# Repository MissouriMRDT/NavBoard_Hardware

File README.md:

# MRDT NavBoard Hardware

## Purpose
The Navigation (Nav) Board is responsible for containing, supplying, and interfacing the equipment required to determine the rover's position and orientation. This board does this by utilizing 2 inertial measurement units (IMUs) and a connection to an external GPS receiver. This data is processed and sent to the rest of the rover via an ethernet connection.
## Design

This revision of the board is a new design, based on the components and connections from the 2022/2023 Rev 2 designs. The goal of this design was to make the board as small as possible, and to mount onto a Teensy 4.1 instead of a raspberry pi.

This design utilizes a 4-layer PCB with holes for M3 mounting screws on 15mm standoffs. The Teensy is soldered onto one side of the board, and all of the smd components are mounted on the other side.

This design also includes an ethernet RJ45 jack for allowing ethernet connectivity to the Teensy.

## Required External Connections
 - +12V
 - GPS (I2C and UART)
 - Teensy 4.1
 - Ethernet

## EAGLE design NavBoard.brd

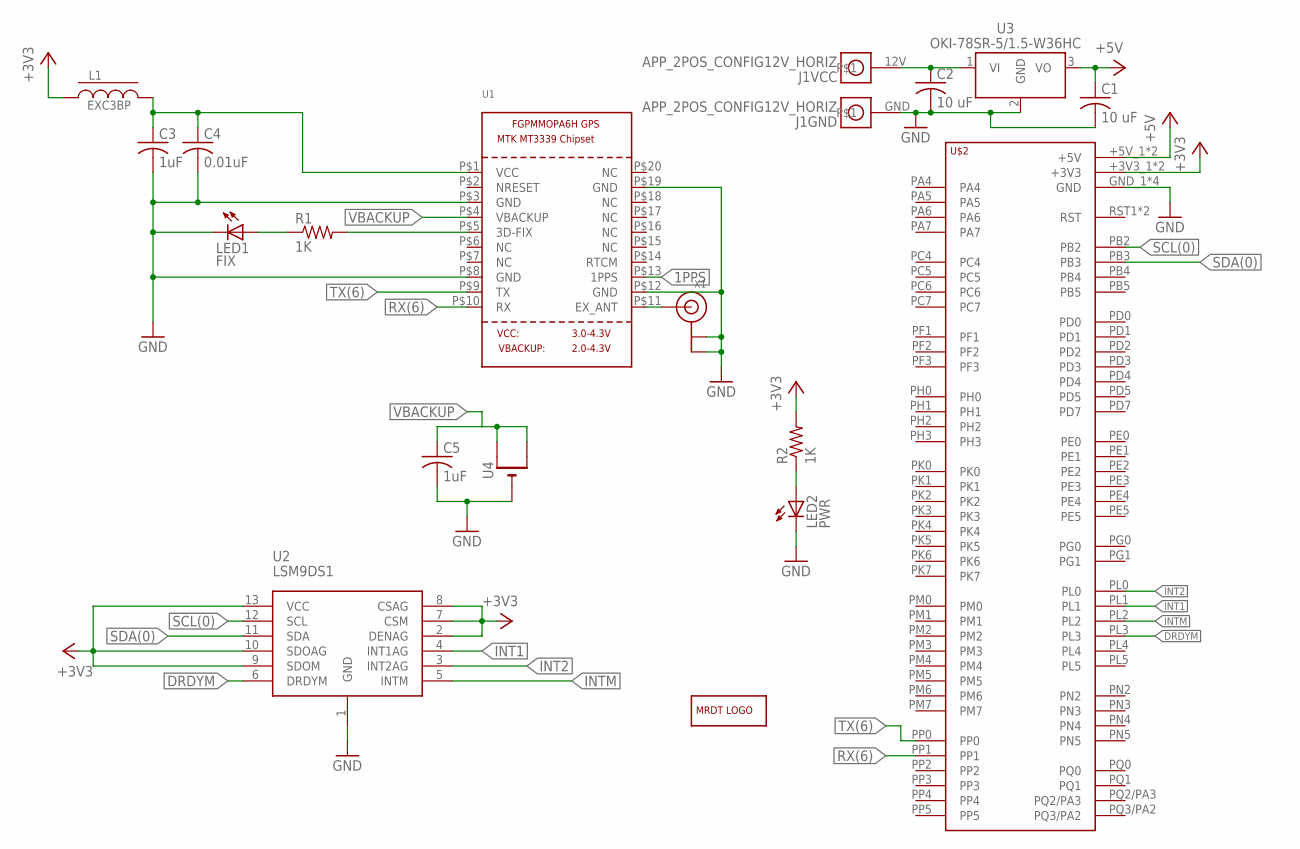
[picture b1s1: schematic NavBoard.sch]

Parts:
C1, C2: 10 uF; C1206
C3, C5: 1uF; C0805
C4: 0.01uF; C0805
J1: APP_2POS_CONFIG12V_HORIZ; APP45_12V_HORIZ_CONFIG
L1: EXC3BP; L0603
LED1: FIX; CHIPLED_0805
LED2: PWR; CHIPLED_0805
LOGO1: MRDT_LOGO
R1, R2: 1K; M0805
U1: GPS_FGPMMOPA6H; FGPMMOPA6H
U2: LSM9DS1; LSM9DS1_BREAKOUT
U3: OKI-78SR-5/1.5-W36HC; OKI-78SR_HORIZ
U4: CR1220SMT; CR1220-SMD
U$2: TIVA-1294; TIVA-C-CONNECTED
X1: ANTENNA_U.FL; U.FL

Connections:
1PPS: U1.P$13 (1PPS)
+3V3: L1.1, R2.2, U2.2 (DENAG), U2.7 (CSM), U2.8 (CSAG), U2.9 (SDOM), U2.10 (SDOAG), U2.13 (VCC), U$2.+3V3_1 (+3V3), U$2.+3V3_2 (+3V3)
+5V: C1.1, U3.3 (VO), U$2.+5V_1 (+5V), U$2.+5V_2 (+5V)
DRDYM: U2.6 (DRDYM), U$2.PL3
GND: C1.2, C2.2, C3.2, C4.2, C5.2, J1.GND, LED1.C, LED2.C, U1.P$3 (GND), U1.P$8 (GND), U1.P$12 (GND), U1.P$19 (GND), U2.1 (GND), U3.2 (GND), U4.-, U$2.GND_1 (GND), U$2.GND_2 (GND), U$2.GND_3 (GND), U$2.GND_4 (GND), X1.1 (GND), X1.2 (GND)
INT1: U2.4 (INT1AG), U$2.PL1
INT2: U2.3 (INT2AG), U$2.PL0
INTM: U2.5 (INTM), U$2.PL2
unnamed: C2.1, J1.12V, U3.1 (VI)
unnamed: LED1.A, R1.1
unnamed: R1.2, U1.P$5 (3D-FIX)
unnamed: LED2.A, R2.1
unnamed: U1.P$11 (EX_ANT), X1.3 (SIGNAL)
unnamed: C3.1, C4.1, L1.2, U1.P$1 (VCC)
RX(6): U1.P$10 (RX), U$2.PP1
SCL(0): U2.12 (SCL), U$2.PB2
SDA(0): U2.11 (SDA), U$2.PB3
TX(6): U1.P$9 (TX), U$2.PP0
VBACKUP: C5.1, U1.P$4 (VBACKUP), U4.+$1 (+), U4.+$2 (+1)

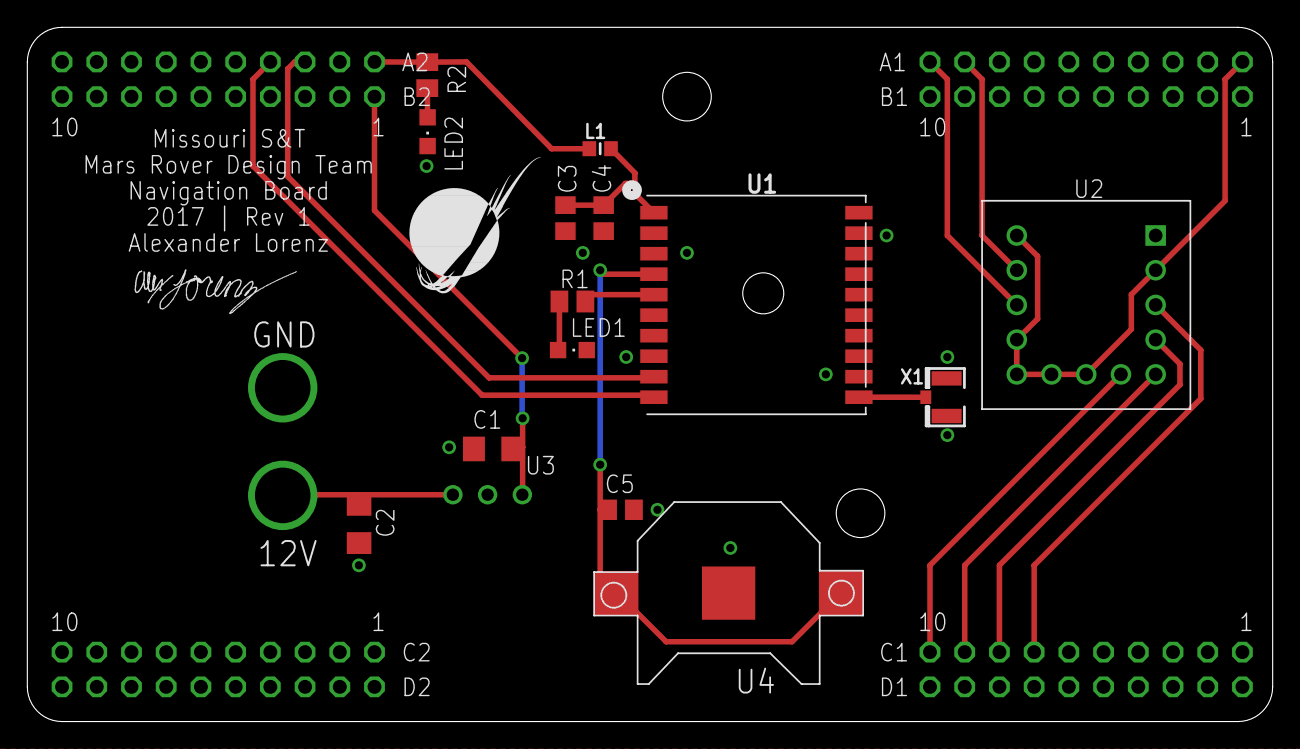
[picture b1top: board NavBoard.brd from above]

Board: 2 copper layers, 91.1 x 50.8 mm, 21 parts (0 on the bottom side), 18 nets.

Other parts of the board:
U$1: SIG
U$3, U$4: #6_SCREW

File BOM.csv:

Part,Value,Device,Package,Description,COLOR1,COLOR2,VOUT
C1,10 uF,C-USC1206,C1206,"CAPACITOR, American symbol",,,
C2,10 uF,C-USC1206,C1206,"CAPACITOR, American symbol",,,
C3,1uF,C-USC0805,C0805,"CAPACITOR, American symbol",,,
C4,0.01uF,C-USC0805,C0805,"CAPACITOR, American symbol",,,
C5,1uF,C-USC0805,C0805,"CAPACITOR, American symbol",,,
J1,APP_2POS_CONFIG12V_HORIZ,APP_2POS_CONFIG12V_HORIZ,APP45_12V_HORIZ_CONFIG,,YELLOW,BLACK,
L1,EXC3BP,EXC3BP,L0603,"gPS Module - MTK MT3339 Chipset, -165dBm sensitivity, 22 channels, 10Hz, auto-select external antenna options",,,
LED1,FIX,LEDCHIPLED_0805,CHIPLED_0805,LED,,,
LED2,PWR,LEDCHIPLED_0805,CHIPLED_0805,LED,,,
LOGO1,MRDT_LOGO,MRDT_LOGO,MRDT_LOGO,,,,
R1,1K,R-US_M0805,M0805,"RESISTOR, American symbol",,,
R2,1K,R-US_M0805,M0805,"RESISTOR, American symbol",,,
U$2,TIVA-1294,TIVA-1294,TIVA-C-CONNECTED,TIVA C CONNECTED LAUNCHPAD,,,
U1,,GPS_FGPMMOPA6H,FGPMMOPA6H,"GPS Module - MTK MT3339 Chipset, -165dBm sensitivity, 22 channels, 10Hz, auto-select external antenna options",,,
U2,LSM9DS1,LSM9DS1,LSM9DS1_BREAKOUT,,,,
U3,OKI-78SR-5/1.5-W36HC,OKI-78SR-5/1.5-W36HC,OKI-78SR_HORIZ,4.95W DC/DC Converter,,,+5v
U4,,CR1220SMT,CR1220-SMD,CR1216/CR1220/CR1225 12mm 3V lithium coin cell,,,
X1,,ANTENNA_U.FL,U.FL,U.FL Antenna Connector,,,

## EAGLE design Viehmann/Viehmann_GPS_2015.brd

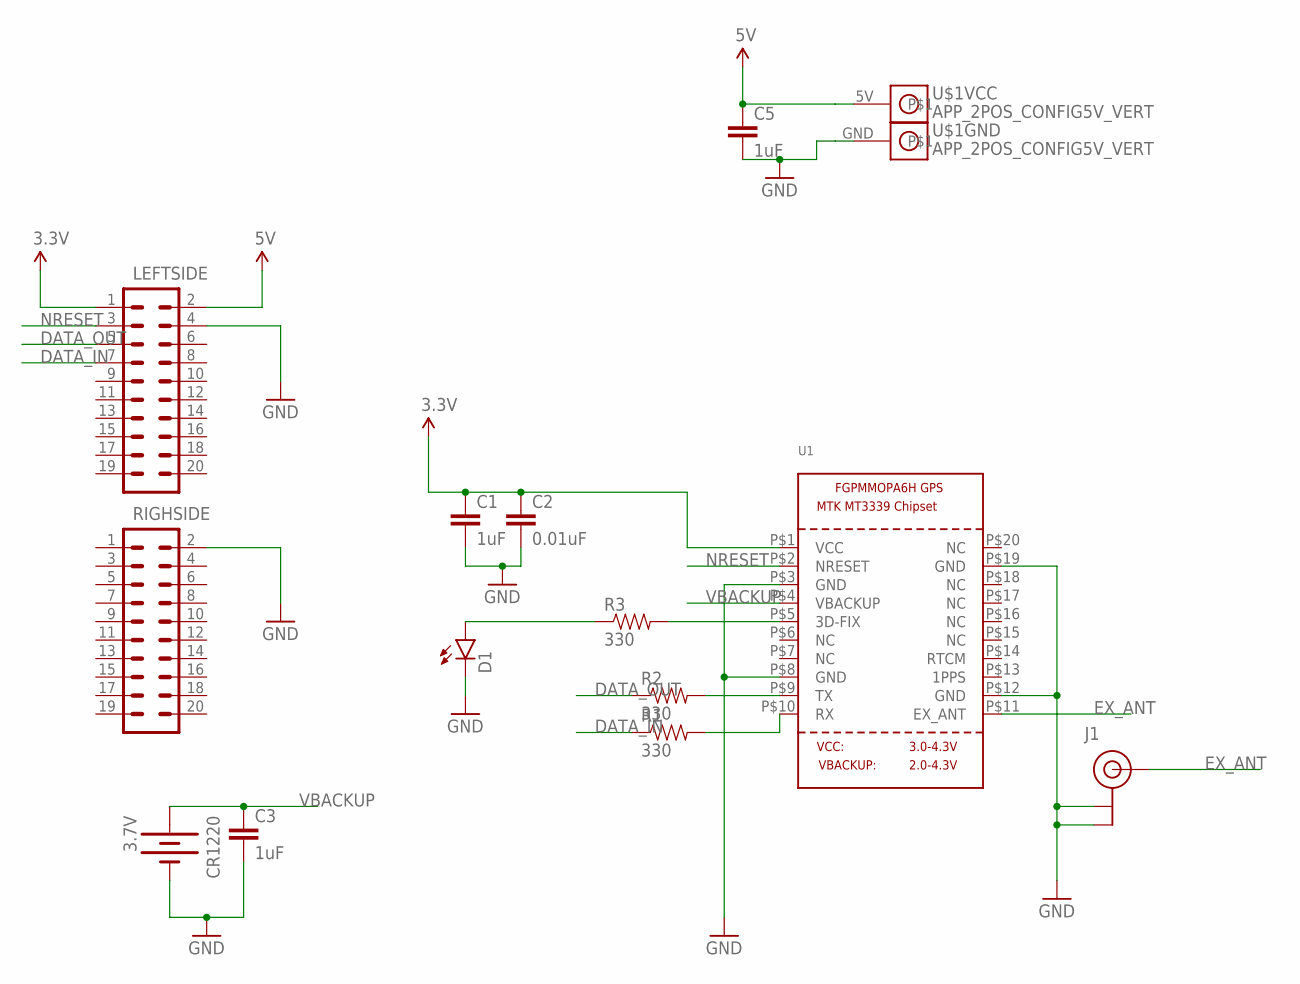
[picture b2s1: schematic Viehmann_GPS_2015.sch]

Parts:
C1, C3, C5: 1uF; 1206
C2: 0.01uF; 1206
CR1220: 3.7V; BATTCON_12MM
D1: LED1206; LED-1206
J1: U.FL
LEFTSIDE: M10X2; 2X10
R1, R2, R3: 330; 1206
RIGHSIDE: M10X2; 2X10
U1: GPS_FGPMMOPA6H; FGPMMOPA6H
U$1: APP_2POS_CONFIG5V_VERT; APP45_5V_VERT_CONFIG

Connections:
3.3V: C1.1, C2.1, LEFTSIDE.1, U1.P$1 (VCC)
5V: C5.1, LEFTSIDE.2, U$1.5V
DATA_IN: LEFTSIDE.7, R1.1
DATA_OUT: LEFTSIDE.5, R2.1
EX_ANT: J1.P$3 (SIGNAL), U1.P$11 (EX_ANT)
GND: C1.2, C2.2, C3.2, C5.2, CR1220.GND (-), D1.C, J1.P$1 (GND), J1.P$2 (GND), LEFTSIDE.4, RIGHSIDE.2, U1.P$3 (GND), U1.P$8 (GND), U1.P$12 (GND), U1.P$19 (GND), U$1.GND
unnamed: R3.2, U1.P$5 (3D-FIX)
unnamed: D1.A, R3.1
unnamed: R2.2, U1.P$9 (TX)
unnamed: R1.2, U1.P$10 (RX)
NRESET: LEFTSIDE.3, U1.P$2 (NRESET)
VBACKUP: C3.1, CR1220.PWR@1 (+), U1.P$4 (VBACKUP)

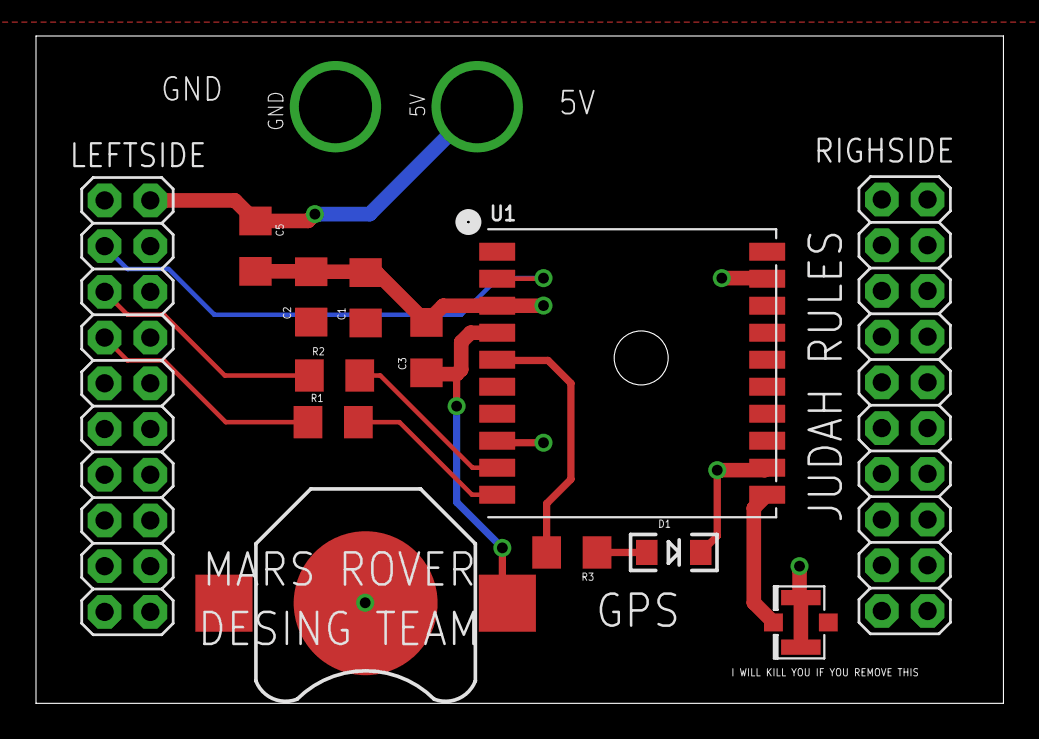
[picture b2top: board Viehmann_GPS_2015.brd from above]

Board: 2 copper layers, 53.7 x 37.1 mm, 14 parts (0 on the bottom side), 12 nets.

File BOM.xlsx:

Qty | Value | Device | Package | Parts | Description | Company
3 |  | GPS_FGPMMOPA6H | FGPMMOPA6H | U1 | GPS Module - MTK MT3339 Chipset, -165dBm sensitivity, 22 channels, 10Hz, auto-s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 | http://www.adafruit.com/products/790
3 |  | LED1206 | LED-1206 | D1 | LEDs | 1206 LED
3 |  | M02PTH | 1X02 | VIN | Standard 2-pin 0.1 header. Use with" | Standard Screw Terminals
6 |  | M10X2 | 2X10 | LEFTSIDE, RIGHTSIDE | This was SPECIALLY designed to be used with our Graphic LCD Backpack. Be sure y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 | 10X2 header pins
3 |  | CAP1206 | 1206 | C2 | Capacitor | 1206 Capacitor
12 | 1uF | CAP1206 | 1206 | C1, C3, C4, C5 | Capacitor | 1206 Capacitor
9 | 330 | RESISTOR1206 | 1206 | R1, R2, R3 | Resistor | 1206 Resistor
3 | CR1220-3.7 | BATTERY12MM | BATTCON_12MM | BATTERY | Battery Holders | https://www.sparkfun.com/products/10592
3 | LD1117#50 | V_REG_LD1117 | SOT223 | V_REG | MIC2920A (http://www.micrel.com/_PDF/mic2920.pdf) - 400mA output LDO Regulator | http://www.digikey.com/scripts/DkSearch/dksus.dll?Detail&ite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
3 | U.FL | U.FL | U.FL | ANT_CONN | SMD antenna connector- WRL-09144 | http://www.digikey.com/product-detail/en/U.FL-R-SMT(01)/H916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

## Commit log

2015-10-05 Added GPS Schematic
    Added my version of the GPS thingy
2015-10-05 Added GPS Schematic
    My version
2015-10-19 Placed the distance between the headers
2015-10-24 Finished first rev of the gps board
    Shout out to board space and Judah
2015-10-26 Revision 1 of the GPS Board
    Super EAGLE Training
2015-10-26 Created my first board!
2015-10-26 Added bill of materials
    Here is the components to be put on the board
2015-10-26 Updated the folder structure
    Gave everyone there one folder
2015-10-26 Added a git ignore
2015-10-26 Updated the git ignore and tested the files
2015-10-31 Added all board files and things
2016-01-22 Updated BOM
2016-01-22 Added 3-Pin Connector
    Give this a look Judah and let me know if you need more stuffs
2016-03-14 swapped power conn to app45 and put backup battery on top, gen'ed gerbers
2016-10-13 Removed unnessasary files and file structure
2016-10-13 Renamed Board and Schematic files
2016-10-13 Deleted Bill of Materials
2016-10-13 Updated the .gitignore
2016-11-05 Added new NavBoard file, Removed old Navigation Board files
2016-11-05 Added LSM9DS1 IMU to circuit
    Wired up the IMU breakout board to Tiva and changed RX and TX notation
    tags to RX(2) and TX(2).
2016-11-05 Completed first version of PCB design and added power connectors and regulator to schematic and board
    Completed first version of board design, added 12v anderson connectors
    to schematic along with 5v regulator and 10 uF capacitors, and changed
    RX(2) and TX(2) to RX(6) and TX(6).
2016-11-07 Finished revision 1 of board design
    Schematic: Connected INTM, INT1, INT2, and DRDYM from IMU to pins PL0
    through PL3 on the Tiva. Added two new capacitors to power input of the
    GPS chip. Added a capacitor to the battery power supply.
    Board: Added top layer ground plane with ground plane stitching, added
    mounting holes for the navigation board, arranged all component names on
    board so they would be visible once they were silk screened, and added
2018-05-03 Added BOM.csv
2018-10-13 GPS chip/LSM9DS1 created
2018-10-13 Fixed libraries
2018-10-13 Remade, finished schematic
2018-10-13 Started editing netlist
2018-10-14 saved wor
2018-10-14 Assigned all parts
2018-10-14 Finalized high lvl schematic
2018-10-16 Fixed cut lines on PCB layout
2018-10-20 Fixed Errors and added a LIDAR
    Some of the gobal labels had to be fixed and I added a LIDAR to the schematic. Also added some .txt files for pdr.
2018-10-20 Made updates to txt files
2018-10-23 Added LIDAR 4SL
2018-10-23 Changed Txt files
2018-10-23 Final PDR edits
2018-10-25 Changed indicators
2018-10-26 PDR Ready
2018-11-03 Added Tracks
2018-11-04 Slight changes to PCB traces
2018-11-11 Finalized Rev1
2018-11-13 Edit traces
2018-11-15 Edit traces before review
2018-11-15 modified gitignore
2018-11-16 After meeting
2018-11-16 Deleted Eagle Files
2018-11-18 Deleted old files, renamed files to NavBoard Hardware
2018-11-18 Renamed more files to NavBoard_Hardware
2018-11-18 Moved txt files and renamed files
2018-11-18 Rename
2018-12-01 fixed file errors
2018-12-01 revised schematic after meeting
2018-12-02 NOTES
2018-12-09 redid files again
2018-12-09 Did good work
2018-12-10 Editied schematic and made PCB
2018-12-10 edit PCB
2018-12-15 Fixed traces
2018-12-15 rev1
2018-12-16 worked on Board
2018-12-16 BOM and other files for review
2018-12-16 just in case push
2018-12-18 fxed gitignore
2019-02-11 added todo
2019-02-15 Updated to rev2 libraries
2019-02-15 updated rev 2 libraries
2019-02-15 generated step file
2019-02-18 Update ToDo rev 2.txt
    Added LiDAR-specific high-level changes needed
2019-02-21 Update ToDo rev 2.txt
    Updates rev2 in regards to LiDAR.
2019-02-25 3v3 lidar
2019-02-26 ATMEGA328P update
2019-02-26 added comments
2019-03-02 Finsihed all changes by Andrew Starting PCB
2019-03-02 Traces and PCB begin
2019-03-02 Retracing PCB for Rev 2
2019-03-03 REV2
2019-03-03 made board super dank
2019-03-03 Board Review
2019-03-03 Push
2019-03-03 CURRENT REVISION
2019-03-03 3.3 to 5 volt converter added
2019-03-03 added footprints
2019-03-03 saved
2019-03-03 molex 2 added
2019-03-03 Added level shifter to board and made traces beautiful
    I, Andre did alot. I sleep now
2019-03-04 Fine tooth comb
2019-03-04 fixed direction of signs
2019-03-04 nitpicking
2019-03-04 PCB UPDATES
2019-03-04 REV 2
2019-03-04 final push
2019-03-04 gerbs
2019-03-04 Final touches
2019-03-04 Added 3.3V output to IMU on layout
2019-03-04 Made many small tweaks
2019-03-05 minor changes and improvements
2019-03-05 BOM MADE
2019-03-05 saved sch
2019-03-05 Fixed DRC Polygons
2019-03-05 Stitched GND plane & gen Gerbs
2019-03-19 Rev 3 start
2019-03-20 Made both sides ground and fixed wires
2019-03-24 Rev 3 Gerbs and Minor Changes made
2020-09-12 created project
2021-01-08 Placed components and started BNO055 schematic
2021-01-09 Completed the schematic for the IMUs but still need to add indicators and have a schematic review.
2021-01-09 Finished Layout but needs review
2021-01-09 Started Layout
2021-01-10 Layout almost finished just need to complete LED traces.
2021-01-10 Finished Layout but I still need to complete the BOM and generate GERBs.
2021-01-10 Completed the board but still needs a review.
2021-01-13 Added readme and fixed serial flags in the schematic
2021-10-09 Duplicated last year's board with a few changes
    BMX160 was replaced with BNO080 and LiDAR circuit was removed. Reorganized schematic and cleaned up some wires.
2021-10-15 Finished wiring BNO080 circuit
    Also changed values of indicator resistors
2021-10-16 Changed BNO080 to I2C communication
2021-10-23 PDF Schematic
    Uploaded PDF Schematic to Github
2021-10-24 Added backup battery for GPS
    Change was discussed in PDR. Also fixed input to BNO080.
2021-11-04 Assigned footprints and started layout
2021-11-15 Finished layout for board reviews
2021-11-16 Board Review Edits
2021-11-16 Deleted old components
2021-11-17 Downloaded footprints and libraries, wired GPS
2021-11-17 Completed schematic
2021-11-18 Completed Layout
2021-11-19 CDR Changes 2
    Ready to release, signatures to be added
2021-11-21 Signature
    Added my signature on the board. Still needs one more.
2021-11-21 Fixed Signature
2021-11-21 Added signature
    Final updates, ready to order
2021-12-30 removed rescue libraries & fixed symbol associations. imported IMU footprints to MRDT_KICAD_LIBRARIES
2022-09-07 Initial pass at stackable arrangement
    Attempting to replace previous board design with 2 daughter boards, using a Teensy 4.1 instead of a Raspberry Pi
2022-09-14 Symbol Stuff
2022-09-14 Fixed broken symbols
2022-09-15 Moved status LEDs to Raspberry Pi GPIO
2022-09-15 Replaced global labels with net labels
2022-09-15 Added title block info, adjusted powerpole connectors
2022-09-15 Added links to IC datasheets
2022-09-15 Added pulldown resistors to unused pins of BHI160B
2022-09-15 Added test points and pulldown resistors to unused pins of ICM-20608
2022-09-15 Routed ICs and their passive components
2022-09-15 Corrected 3D models, added model of Raspberry Pi
2022-09-15 Routed most components
    Some power traces, and LEDs remain
2022-09-16 Component placement done (except LEDs), redesign of schematic pages, started documentation presentations
    Leaving @katdun14 and @nvngx responsible for routing the status LEDs.
2022-09-17 Added ground vias for added isolation in substrate, worked on schematic review 1 powerpoint
2022-09-17 Added Information To Voltage Regulator Component Sheets, Improved Schematic Review 1 Powerpoint
2022-09-17 Improved Schematic
2022-09-17 Swapped TX and RX for GPS pins
2022-09-18 Redesigned layoput
2022-09-22 Routed LEDs
2022-09-22 Added name and moved words
2022-09-23 Adjusted LED silkscreen
2022-09-23 Adjusted silkscreen for various components
2022-09-23 Adjusted copper pour
2022-09-23 Updated sheet title info
2022-09-23 Updated Schematic Review 1 Powerpoint
2022-09-23 Corrected accelerometer regulator capacitors
2022-09-23 Included BOM to Schematic Review 1 PowerPoint
2022-09-23 Added signatures to pcb silkscreen
2022-09-24 Added 0ohm resistors to I2C
2022-09-26 Added signage for TSR power supplies
2022-10-01 Made PDF
2022-10-07 Created adapter symbols and footprints
2022-10-07 Added connectors, cleaned up file directory
2022-10-07 Updated BMI component sheet from Navboard_2023_rev2
2022-10-07 Most schematic connections completed
2022-10-07 Annotated Schematic, assigned footprints, recovered accelerometer footprints
2022-10-07 Fixed pinout of 24pin-to-16pin adapter footprint
2022-10-07 Corrected pinout of RJ45 symbol, squashed some bugs
2022-10-07 Progress with PCB layout
2022-10-07 Resized Ethernet to 2.54mm
2022-10-08 Placed and aligned all headers
2022-10-08 Placed OKI SMD components, aligned ethernet pins
2022-10-09 Completed routing, added 3D models to IMUs
2022-10-09 Adjusted silkscreen labels
2022-10-09 Added 3D models for pin sockets and headers
2022-10-09 Rearranged PCBs, added mouse bites
2022-10-09 Annotated schematic pages
2022-10-09 Added signage to pcb silkscreen
2022-10-09 Generated 3D renderings, animation, and schematic review PowerPoint
2022-10-09 Plotted schematic to pdf
2022-11-01 Initial changes and prototyping the new layout
2022-11-01 Rearranged schematic
    I realize now that this is a dumb idea...
    Going to redesign the board so the teensy just sits on top
2022-11-03 Decided on pcb layout
2022-11-03 Realized this could all fit on a single board
2022-11-03 Most connections made on schematic
2022-11-03 Completed routing, finalized schematic
2022-11-03 Updated schematic page text
2022-11-04 Made I2C pulldown resistors pullup instead
2022-11-05 Square powerpole footprints
2022-11-05 Cleaned up unnecessary files
2022-11-19 generated gerbs
2022-11-19 forgot to zip gerbs
2022-11-25 Added pcb dimensions, images of board, readme files
2022-11-25 Added images to readme files
2022-11-25 Updated repo with up-to-date schematic and pcb
    Not sure why this happened, but the repo should be up to date now. We should try to cancel the PCB order and reupload this board if that's still possible.
2022-11-25 Generated images, edited Readme files

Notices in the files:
parts and their libraries:
SparkFun-Resistors: Licensing: Creative Commons ShareAlike 4.0 International - https://creativecommons.org/licenses/by-sa/4.0
